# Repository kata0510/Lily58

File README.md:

# Lily58
Lily58 is 6*4+4keys column-staggered split keyboard.

## [Document Site Here](https://kata0510.github.io/Lily58-Document/)

# Type

- Lily58 Pro
  - [PCB Data](https://github.com/kata0510/Lily58/tree/master/Pro/PCB)
  - [BuildGuide JP](https://kata0510.github.io/Lily58-Document/Lily58_Pro_BG/)
  - [BuildGuide EN](https://github.com/kata0510/Lily58/blob/master/Pro/Doc/buildguide_en.md)
  - [BuildGuide IT](https://github.com/kata0510/Lily58/blob/master/Pro/Doc/buildguide_it.md)
  - [Shop(Yushakobo)](https://yushakobo.jp/shop/lily58-pro/)
- Lily58 Lite Rev2
  - [BuildGuide(YouTube)](https://www.youtube.com/watch?v=t6HLQvqlsVM)
  - [BuildInfo](https://kata0510.github.io/Lily58-Document/Lily58_Lite_Rev2_help.md)
  - [Shop(BOOTH)](https://booth.pm/ja/items/1963895)
  - [Shop(Yushakobo)](https://yushakobo.jp/shop/consign_lily58-lite-rev2/)
- Lily58(Old)
  - [PCB Data](https://github.com/kata0510/Lily58/tree/master/pcb)
  - [BuildGuide](https://kata0510.github.io/Lily58-Document/Lily58_BG/)
- Lily58 Lite Rev1(Old)
  - [PCB Data](https://github.com/kata0510/Lily58/tree/master/pcb)
  - [BuildGuide](https://kata0510.github.io/Lily58-Document/Lily58_Lite_BG/)

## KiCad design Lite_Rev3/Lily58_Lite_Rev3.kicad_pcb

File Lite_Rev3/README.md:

# Lily58 Lite Rev3

### description
- Controller: RP2040-Zero
- Firmware: QMK Firmware

### Assembly Guide
- https://docs.liliums.net/lily58-lite-rev3/about/ (RP2040 installed kit Version)

### Shop
- https://shop.liliums.net/products/lily58-lite-rev3
- https://shop.yushakobo.jp/products/9651

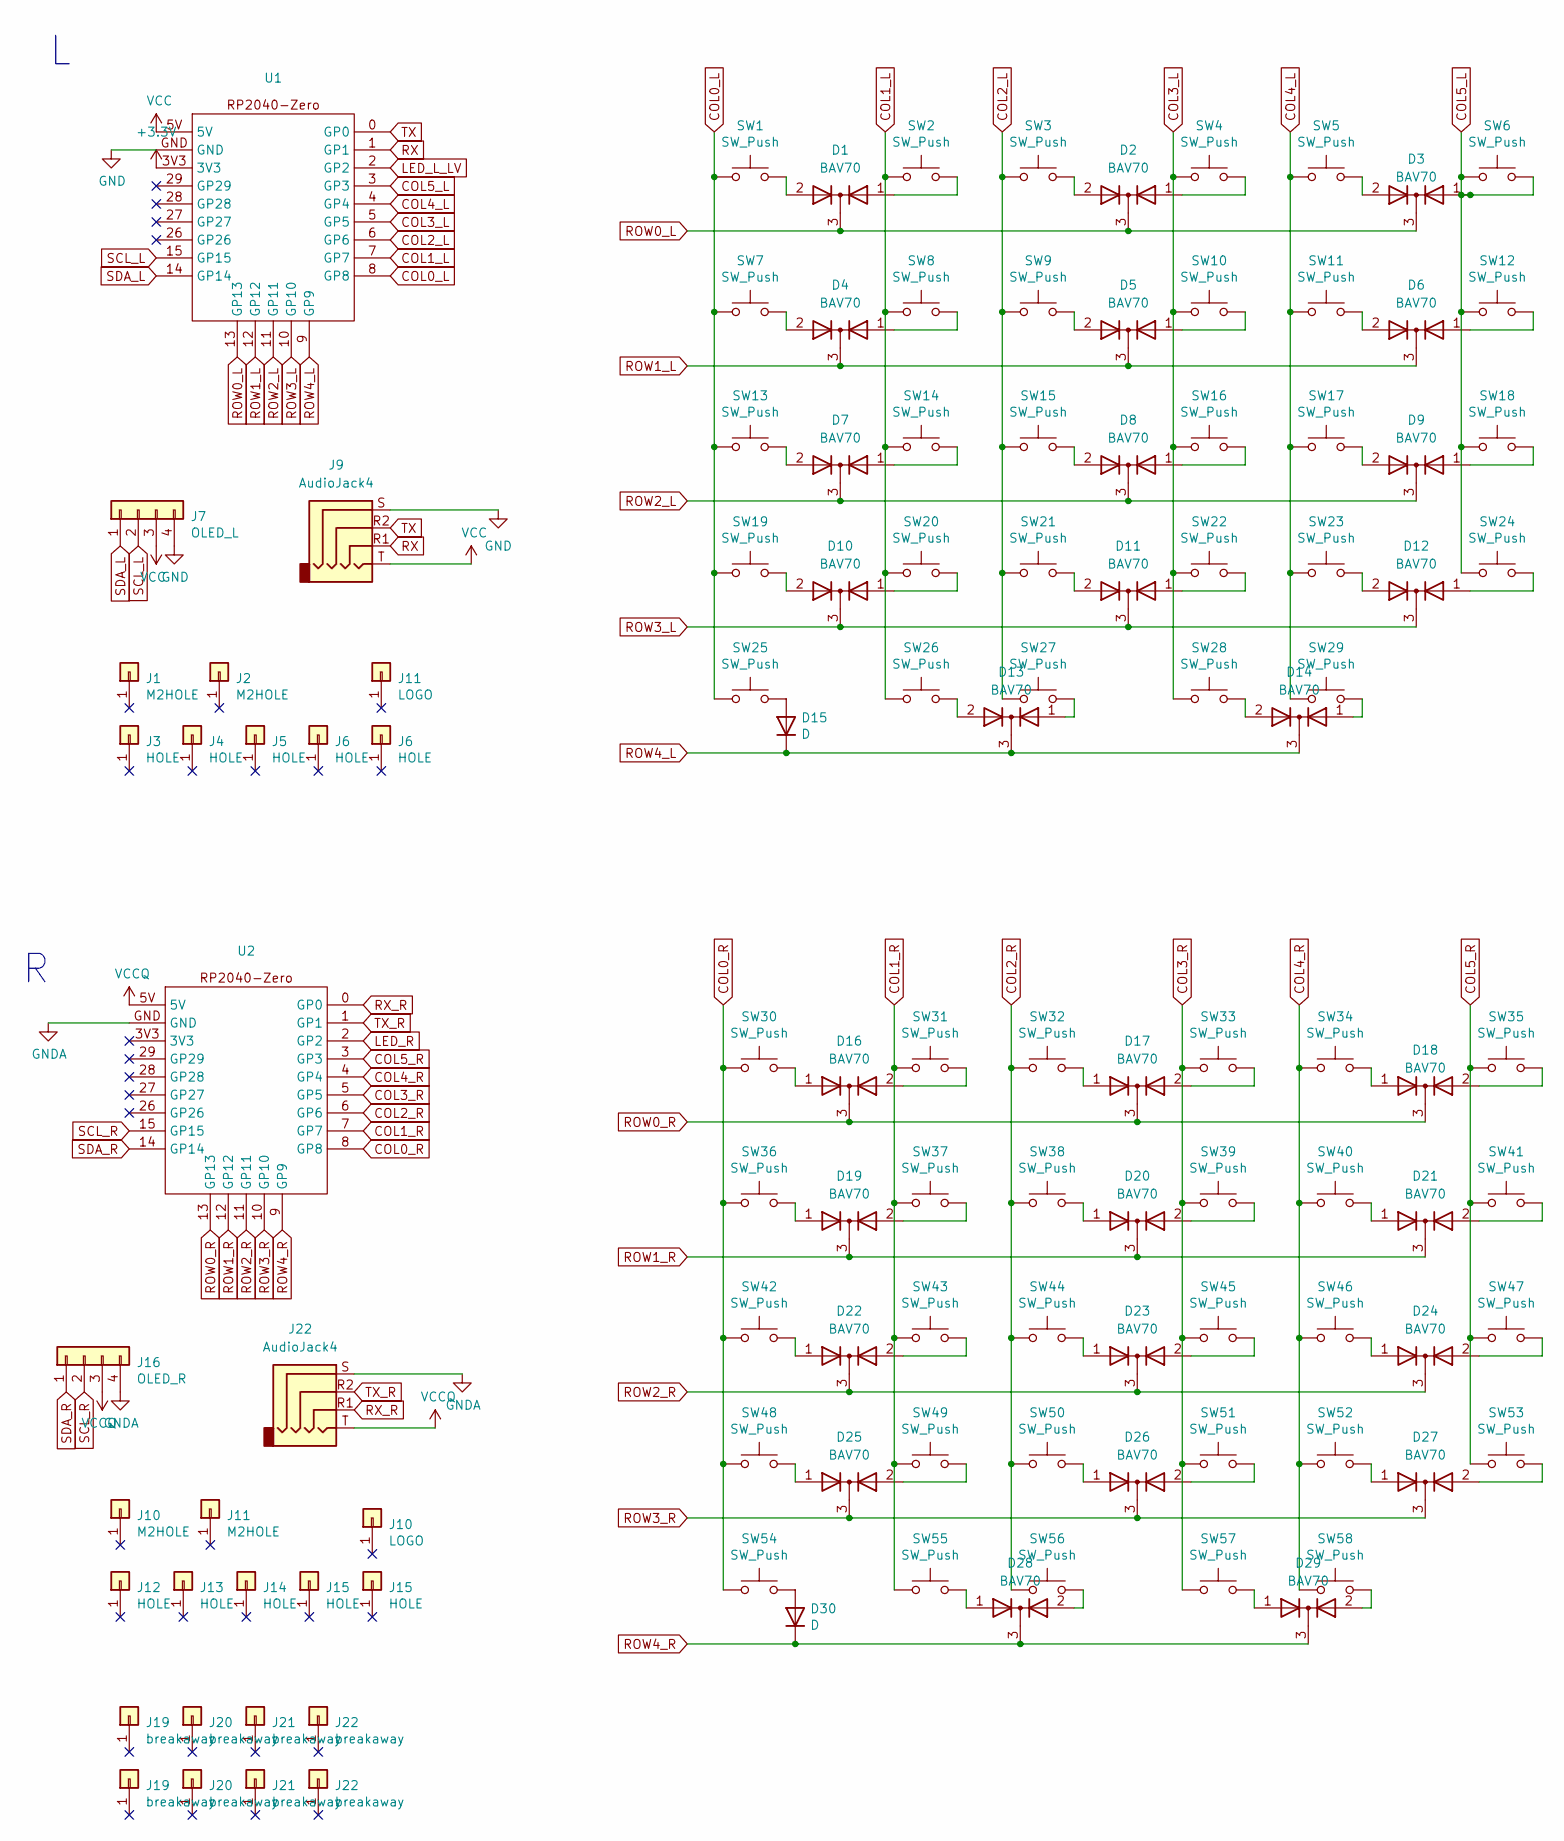
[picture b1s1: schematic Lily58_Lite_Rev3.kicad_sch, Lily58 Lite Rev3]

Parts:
D1, D2, D3, D4, D5, D6, D7, D8, D9, D10, D11, D12, D13, D14, D16, D17, D18, D19, D20, D21, D22, D23, D24, D25, D26, D27, D28, D29: BAV70; SOT-23
D15, D30: D; D_SOD-123
J1, J2, J11: M2HOLE; M2_HOLE_PCB
J3, J4, J5, J6, J12, J13, J14, J15: HOLE; HOLE_M2_TH
J7: OLED_L; OLED_4Pin
J9: AudioJack4; PJ-320
J10: LOGO; lily58_logo_2
J16: OLED_R; OLED_4Pin
J19, J20, J21, J22: breakaway; breakaway04
SW1, SW2, SW3, SW4, SW5, SW6, SW7, SW8, SW9, SW10, SW11, SW12, SW13, SW14, SW15, SW16, SW17, SW18, SW19, SW20, SW21, SW22, SW23, SW24, SW25, SW26, SW27, SW28, SW29, SW30, SW31, SW32, SW33, SW34, SW35, SW36, SW37, SW38, SW39, SW40, SW41, SW42, SW43, SW44, SW45, SW46, SW47, SW48, SW49, SW50, SW51, SW52, SW53, SW54, SW55, SW56, SW57, SW58: SW_Push; MX_HOLE
U1, U2: RP2040-Zero_bottom

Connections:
+3.3V: U1.3V3
COL0_L: SW1.1, SW7.1, SW13.1, SW19.1, SW25.1, U1.8 (GP8)
COL0_R: SW30.1, SW36.1, SW42.1, SW48.1, SW54.1, U2.8 (GP8)
COL1_L: SW2.1, SW8.1, SW14.1, SW20.1, SW26.1, U1.7 (GP7)
COL1_R: SW31.1, SW37.1, SW43.1, SW49.1, SW55.1, U2.7 (GP7)
COL2_L: SW3.1, SW9.1, SW15.1, SW21.1, SW27.1, U1.6 (GP6)
COL2_R: SW32.1, SW38.1, SW44.1, SW50.1, SW56.1, U2.6 (GP6)
COL3_L: SW4.1, SW10.1, SW16.1, SW22.1, SW28.1, U1.5 (GP5)
COL3_R: SW33.1, SW39.1, SW45.1, SW51.1, SW57.1, U2.5 (GP5)
COL4_L: SW5.1, SW11.1, SW17.1, SW23.1, SW29.1, U1.4 (GP4)
COL4_R: SW34.1, SW40.1, SW46.1, SW52.1, SW58.1, U2.4 (GP4)
COL5_R: SW35.1, SW41.1, SW47.1, SW53.1, U2.3 (GP3)
GND: J7.4, J9.S, U1.GND
GNDA: J16.4, J22.S, U2.GND
LED_L_LV: U1.2 (GP2)
LED_R: U2.2 (GP2)
unnamed: D1.1 (A), SW2.2
unnamed: D1.2 (A), SW1.2
unnamed: D2.1 (A), SW4.2
unnamed: D2.2 (A), SW3.2
unnamed: D3.2 (A), SW5.2
unnamed: D4.1 (A), SW8.2
unnamed: D4.2 (A), SW7.2
unnamed: D5.1 (A), SW10.2
unnamed: D5.2 (A), SW9.2
unnamed: D6.1 (A), SW12.2
unnamed: D6.2 (A), SW11.2
unnamed: D7.1 (A), SW14.2
unnamed: D7.2 (A), SW13.2
unnamed: D8.1 (A), SW16.2
unnamed: D8.2 (A), SW15.2
unnamed: D9.1 (A), SW18.2
unnamed: D9.2 (A), SW17.2
unnamed: D10.1 (A), SW20.2
unnamed: D10.2 (A), SW19.2
unnamed: D11.1 (A), SW22.2
unnamed: D11.2 (A), SW21.2
unnamed: D12.1 (A), SW24.2
unnamed: D12.2 (A), SW23.2
unnamed: D13.1 (A), SW27.2
unnamed: D13.2 (A), SW26.2
unnamed: D14.1 (A), SW29.2
unnamed: D14.2 (A), SW28.2
unnamed: D15.2 (A), SW25.2
unnamed: D16.1 (A), SW30.2
unnamed: D16.2 (A), SW31.2
unnamed: D17.1 (A), SW32.2
unnamed: D17.2 (A), SW33.2
unnamed: D18.1 (A), SW34.2
unnamed: D18.2 (A), SW35.2
unnamed: D19.1 (A), SW36.2
unnamed: D19.2 (A), SW37.2
unnamed: D20.1 (A), SW38.2
unnamed: D20.2 (A), SW39.2
unnamed: D21.1 (A), SW40.2
unnamed: D21.2 (A), SW41.2
unnamed: D22.1 (A), SW42.2
unnamed: D22.2 (A), SW43.2
unnamed: D23.1 (A), SW44.2
unnamed: D23.2 (A), SW45.2
unnamed: D24.1 (A), SW46.2
unnamed: D24.2 (A), SW47.2
unnamed: D25.1 (A), SW48.2
unnamed: D25.2 (A), SW49.2
unnamed: D26.1 (A), SW50.2
unnamed: D26.2 (A), SW51.2
unnamed: D27.1 (A), SW52.2
unnamed: D27.2 (A), SW53.2
unnamed: D28.1 (A), SW55.2
unnamed: D28.2 (A), SW56.2
unnamed: D29.1 (A), SW57.2
unnamed: D29.2 (A), SW58.2
unnamed: D30.2 (A), SW54.2
RESET_L: U1.26 (GP26)
RESET_R: U2.26 (GP26)
ROW0_L: D1.3 (K), D2.3 (K), D3.3 (K), U1.13 (GP13)
ROW0_R: D16.3 (K), D17.3 (K), D18.3 (K), U2.13 (GP13)
ROW1_L: D4.3 (K), D5.3 (K), D6.3 (K), U1.12 (GP12)
ROW1_R: D19.3 (K), D20.3 (K), D21.3 (K), U2.12 (GP12)
ROW2_L: D7.3 (K), D8.3 (K), D9.3 (K), U1.11 (GP11)
ROW2_R: D22.3 (K), D23.3 (K), D24.3 (K), U2.11 (GP11)
ROW3_L: D10.3 (K), D11.3 (K), D12.3 (K), U1.10 (GP10)
ROW3_R: D25.3 (K), D26.3 (K), D27.3 (K), U2.10 (GP10)
ROW4_L: D13.3 (K), D14.3 (K), D15.1 (K), U1.9 (GP9)
ROW4_R: D28.3 (K), D29.3 (K), D30.1 (K), U2.9 (GP9)
RX: J9.R1, U1.1 (GP1)
RX_R: J22.R1, U2.0 (GP0)
SCL_L: J7.2, U1.15 (GP15)
SCL_R: J16.2, U2.15 (GP15)
SDA_L: J7.1, U1.14 (GP14)
SDA_R: J16.1, U2.14 (GP14)
TX: J9.R2, U1.0 (GP0)
TX_R: J22.R2, U2.1 (GP1)
VCC: J7.3, J9.T, U1.5V
VCCQ: J16.3, J22.T, U2.5V

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
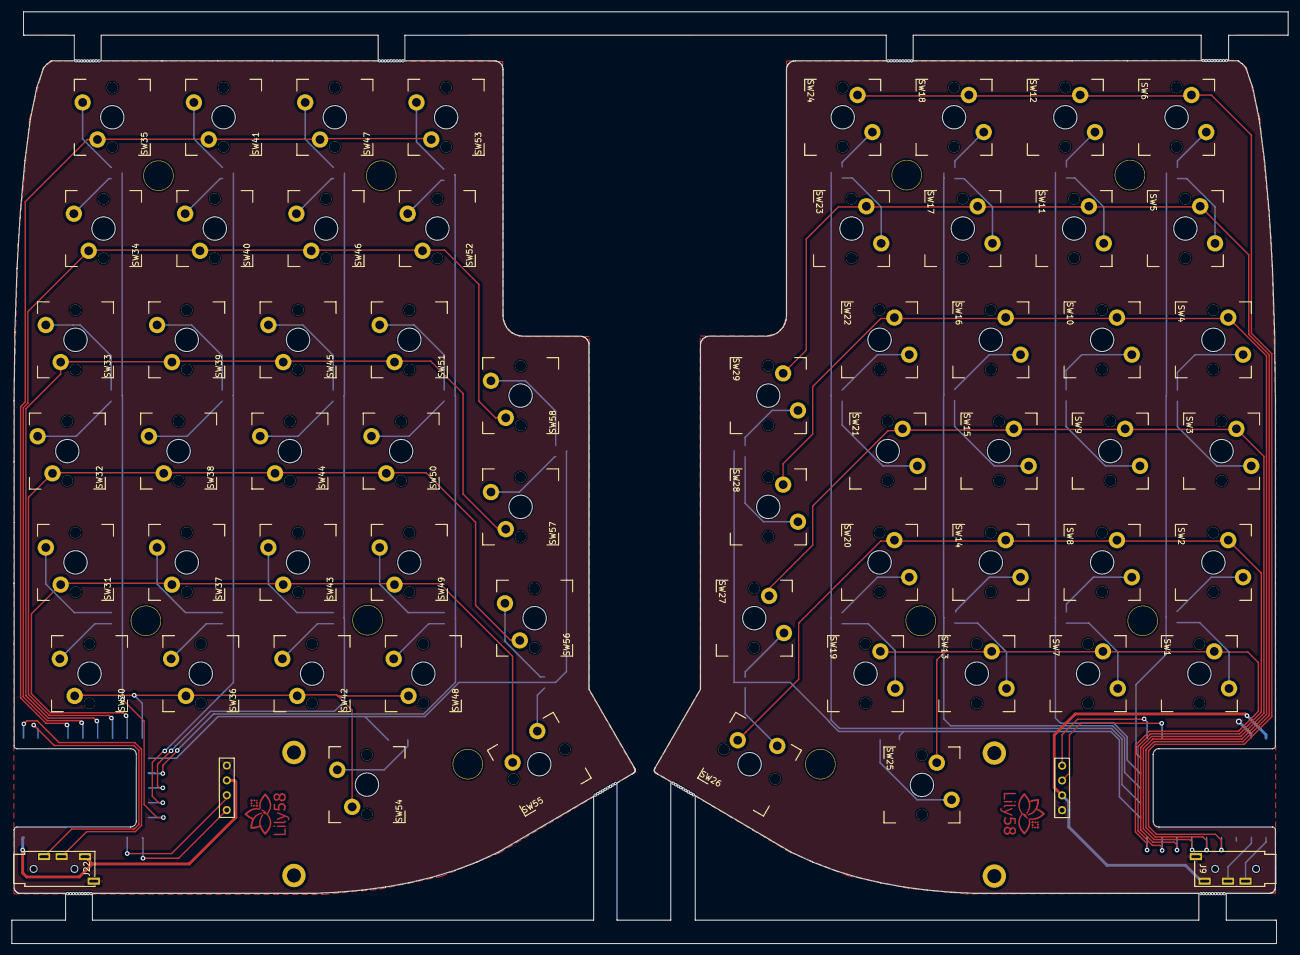
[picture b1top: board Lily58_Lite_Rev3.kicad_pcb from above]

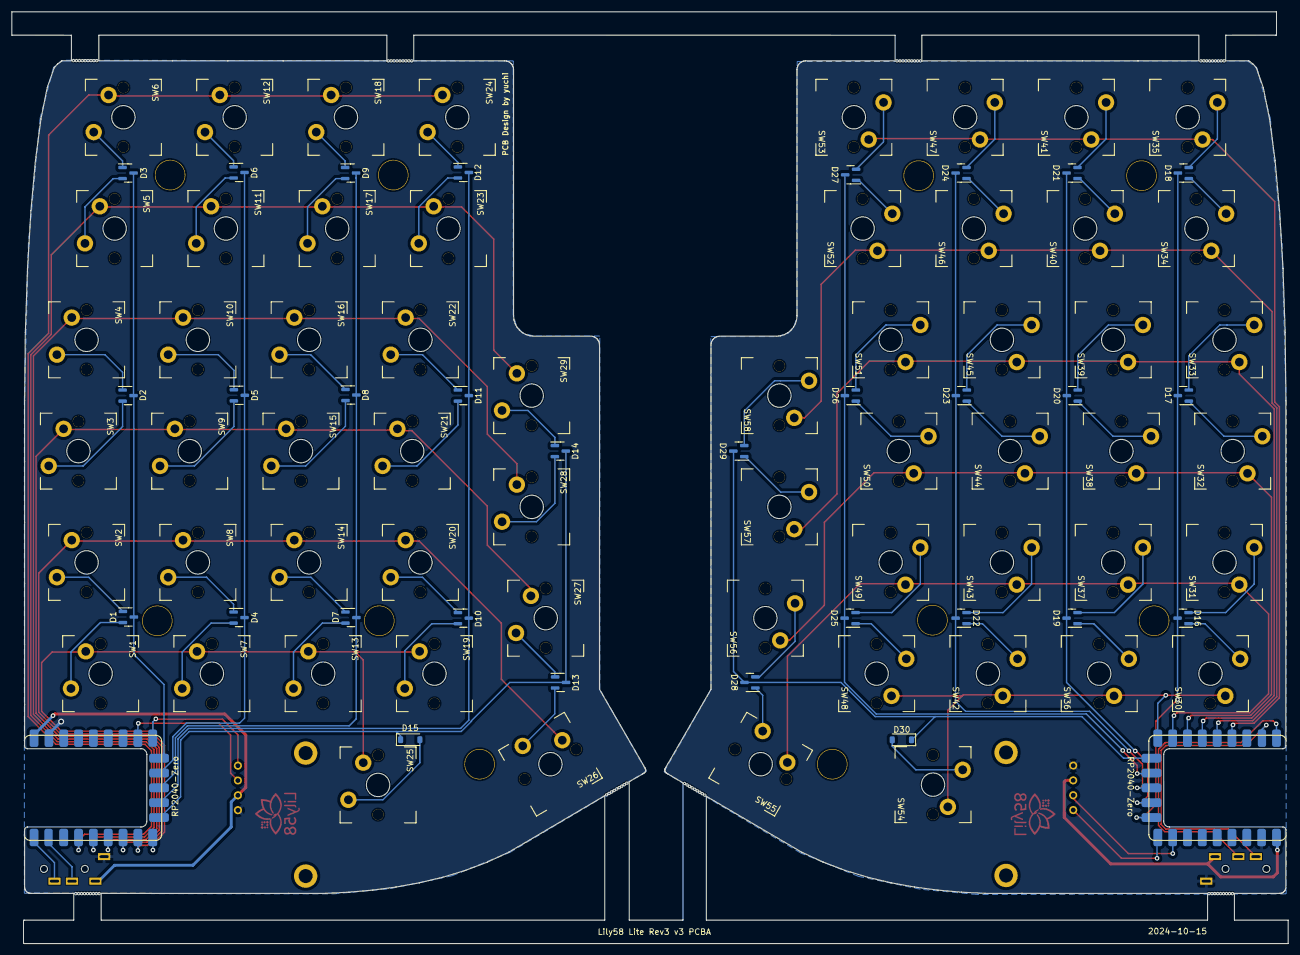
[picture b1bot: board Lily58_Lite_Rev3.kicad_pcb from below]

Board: 2 copper layers, 218.5 x 159.5 mm, 118 parts (34 on the bottom side), 92 nets.

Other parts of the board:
J8, J17, J18, J25, J26: breakaway; breakaway04
J23, J24: HOLE; HOLE_M2_TH_5mm
L01, L02: LOGO; lily58_logo_2

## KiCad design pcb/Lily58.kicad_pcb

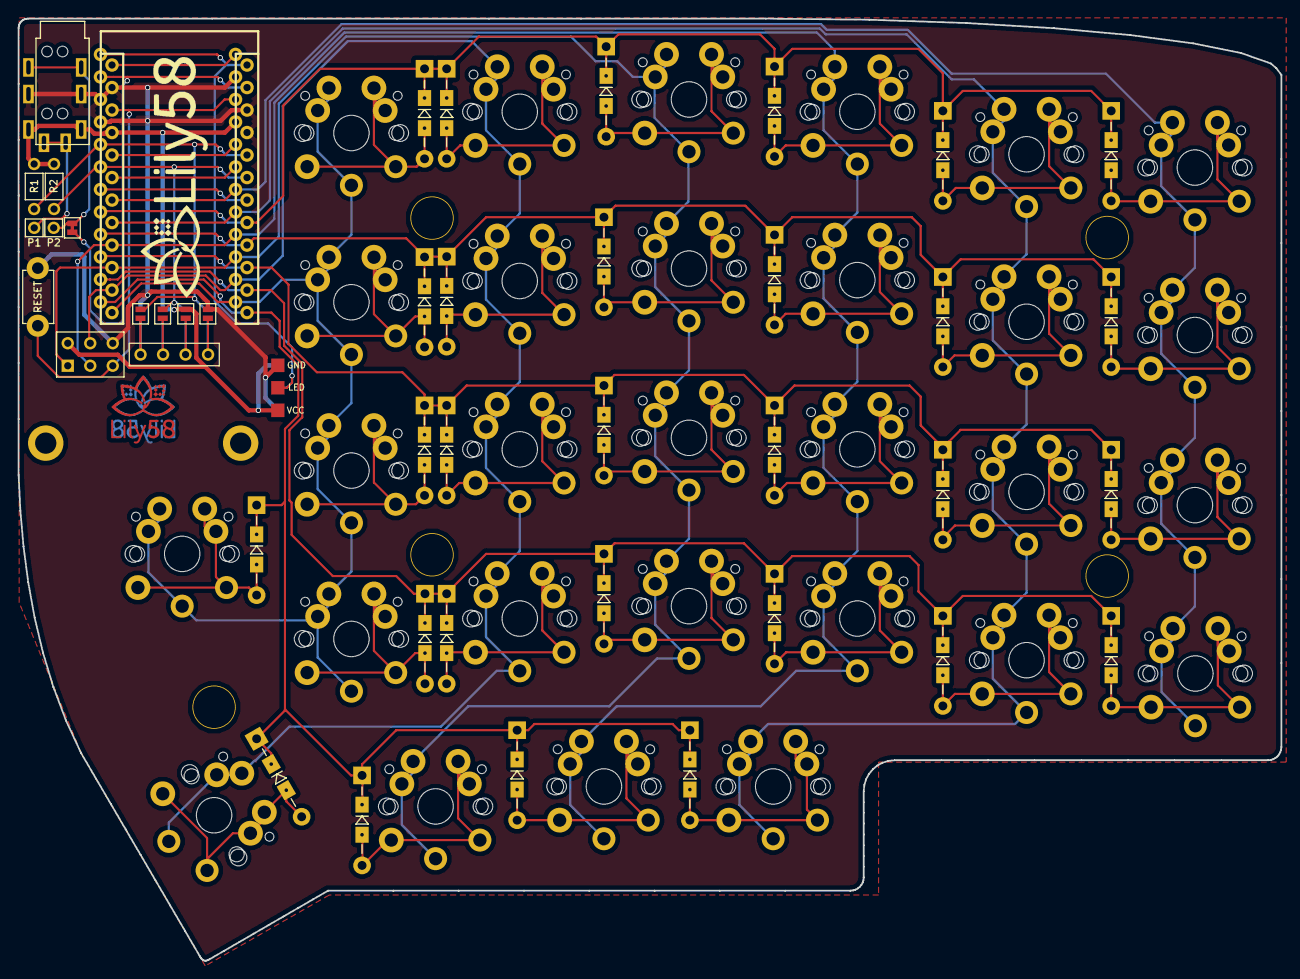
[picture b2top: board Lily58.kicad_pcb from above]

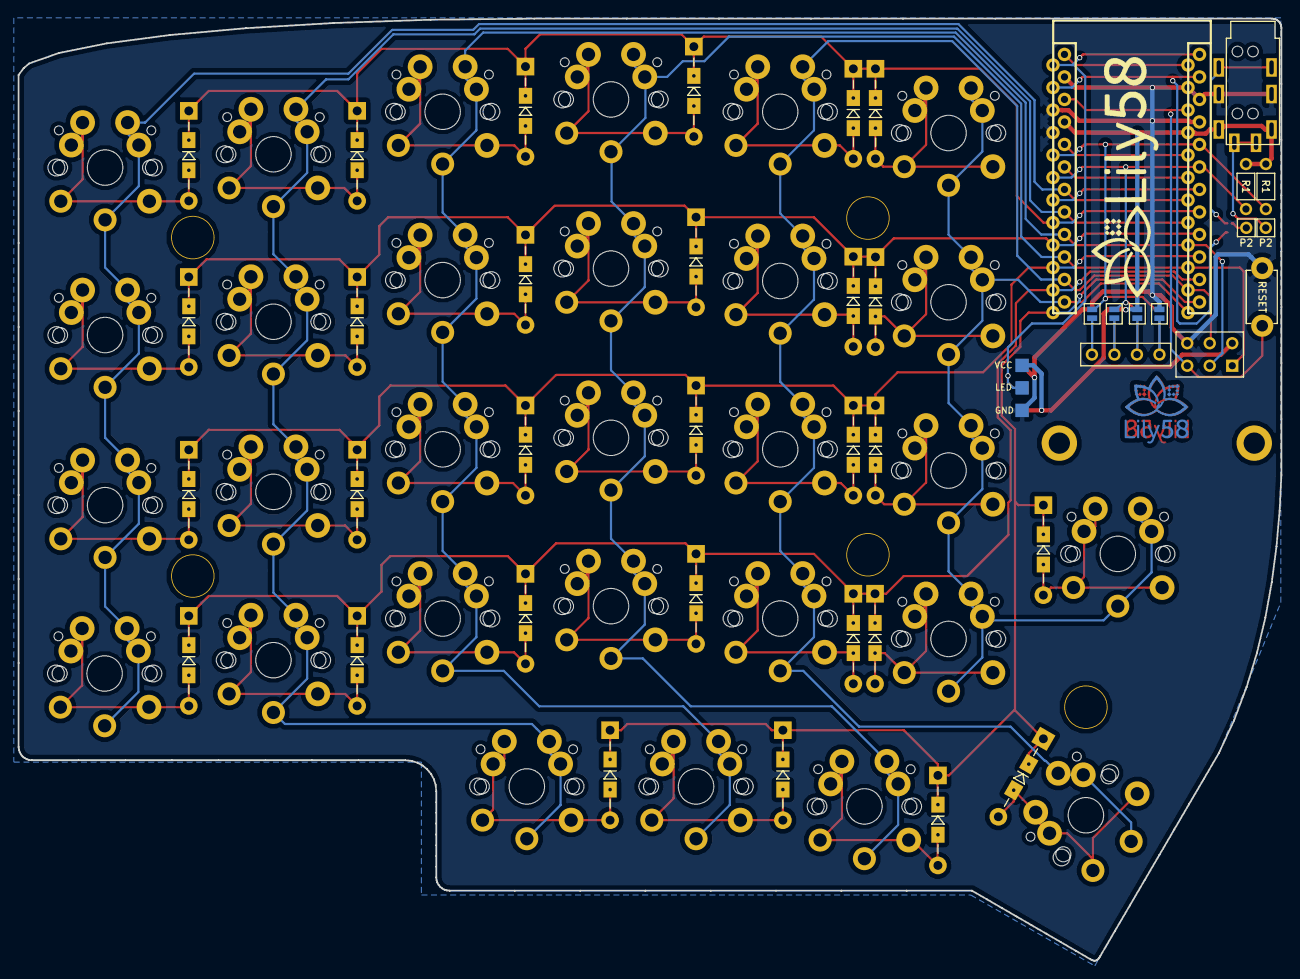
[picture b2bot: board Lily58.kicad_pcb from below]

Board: 2 copper layers, 142.5 x 106.3 mm, 84 parts (4 on the bottom side), 53 nets.

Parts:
D1, D2, D3, D4, D5, D6, D7, D8, D9, D10, D11, D12, D13, D14, D15, D16, D17, D18, D19, D20, D21, D22, D23, D24, D25, D26, D27, D28, D29: D; Diode_TH_SOD123
J1: LED; StripLED
J2: 4PIN; MJ-4PP-9
JP1, JP2, JP3, JP4, JP5, JP6, JP7, JP8: Jumper
OLED: OLED; MY_SIL-4
P1, P2: i2c_pin; 1pin_conn
P3: ICSP
R1, R2: R; RESISTOR_mini
RSW1: SW_RST; TACT_SWITCH_TVBP06
SW1, SW2, SW3, SW4, SW5, SW6, SW7, SW8, SW9, SW10, SW11, SW12, SW13, SW14, SW15, SW16, SW17, SW18, SW19, SW20, SW21, SW22, SW23, SW24, SW25, SW27, SW28, SW29: SW_PUSH; MX_PG1350-Under_FLIP_HOLES_18mm
SW26: SW_PUSH; MX_PG1350-Under_FLIP_HOLES_27mm
TH1, TH2: HOLE; M2_HOLE_PCB
TH3, TH4, TH5, TH6, TH7: HOLE; HOLE_M2_TH
U1: ProMicro; ProMicro_rev2
W1: jumper; jumper_data

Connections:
DATA: U1.2, W1.1
GND: J1.3, J2.2, JP1.2, JP8.2, P3.6, RSW1.1, U1.3, U1.4, U1.23
LED: J1.2, U1.1
unnamed: D1.2, SW1.2
unnamed: D2.2, SW2.2
unnamed: D3.2, SW3.2
unnamed: D4.2, SW4.2
unnamed: D5.2, SW5.2
unnamed: D6.2, SW6.2
unnamed: D7.2, SW7.2
unnamed: D8.2, SW8.2
unnamed: D9.2, SW9.2
unnamed: D10.2, SW10.2
unnamed: D11.2, SW11.2
unnamed: D12.2, SW12.2
unnamed: D13.2, SW13.2
unnamed: D14.2, SW14.2
unnamed: D15.2, SW15.2
unnamed: D16.2, SW16.2
unnamed: D17.2, SW17.2
unnamed: D18.2, SW18.2
unnamed: D19.2, SW19.2
unnamed: D20.2, SW20.2
unnamed: D21.2, SW21.2
unnamed: D22.2, SW22.2
unnamed: D23.2, SW23.2
unnamed: D24.2, SW24.2
unnamed: D25.2, SW25.2
unnamed: D26.2, SW26.2
unnamed: D27.2, SW27.2
unnamed: D28.2, SW28.2
unnamed: D29.2, SW29.2
unnamed: J2.3, P2.1, W1.2
unnamed: J2.4, P1.1
unnamed: JP1.1, JP5.1, OLED.4
unnamed: JP2.1, JP6.1, OLED.3
unnamed: JP3.1, JP7.1, OLED.2
unnamed: JP4.1, JP8.1, OLED.1
RESET: P3.5, RSW1.2, U1.22
SCL: JP3.2, JP6.2, R2.2, U1.6
SDA: JP4.2, JP5.2, R1.2, U1.5
VCC: J1.1, J2.1, JP2.2, JP7.2, P3.2, R1.1, R2.1, U1.21
col0: SW6.1, SW12.1, SW18.1, SW24.1, U1.18
col1: SW5.1, SW11.1, SW17.1, SW23.1, SW29.1, U1.17
col2: P3.3, SW4.1, SW10.1, SW16.1, SW22.1, SW28.1, U1.16
col3: P3.1, SW3.1, SW9.1, SW15.1, SW21.1, SW27.1, U1.15
col4: P3.4, SW2.1, SW8.1, SW14.1, SW20.1, SW26.1, U1.14
col5: SW1.1, SW7.1, SW13.1, SW19.1, SW25.1, U1.13
row0: D1.1, D2.1, D3.1, D4.1, D5.1, D6.1, U1.8
row1: D7.1, D8.1, D9.1, D10.1, D11.1, D12.1, U1.9
row2: D13.1, D14.1, D15.1, D16.1, D17.1, D18.1, U1.10
row3: D19.1, D20.1, D21.1, D22.1, D23.1, D24.1, U1.11
row4: D25.1, D26.1, D27.1, D28.1, D29.1, U1.12

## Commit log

2018-08-21 add PCB
2018-08-21 add case data
2018-08-29 fix case
2018-09-06 update other
2018-09-07 Add LICENSE
2018-09-11 fix and update README
2018-10-13 add buildguide
2018-10-21 file fix
2018-10-22 fix PCB
2018-10-22 buildguide add keymap
2018-10-25 README typo fix
2018-11-09 add doc
2018-11-21 Update Document
2018-12-26 add pro doc
2018-12-31 Lily58Pro Buildguide Update
2019-01-06 Update ProBuildguide
2019-01-13 Update BuildGuide
2019-01-30 Pro BuildGuide Update
2019-01-30 fix buildguide
2019-02-05 Add Lily58 Pro PCB Data
2019-02-23 Add Lily58 Pro PCBData
2019-02-23 Lily58 PCBData update
2019-02-28 update pro buildguide
2019-03-01 Pro Buildguide fix
2019-03-01 README Photo Update
2019-06-05 Add English translation of the build guide for the Pro kit. I don't speak Japanese, so this is a rough translation based on Google Translate and some experience building this board.
2019-07-02 Update Lily58_Lite Buildguide
2019-07-20 Update buildguide_en.md
    remove wrong space in make rule.
2019-07-20 Update buildguide_en.md
    actually also space after colon should be removed.
2019-07-25 fix lily58 lite buildguide
2019-08-20 Update Lily58 Lite buildguide
2020-04-30 add lite_rev2 info
2020-05-02 update lite_rev2 info
2020-05-16 Add first rev of the Lily58L build guide
2020-05-16 Add firmware link to readme
2020-06-03 Added section for rotary encoder
2020-07-21 Correctly formats nested list
2020-07-28 Update Lite LiteRev2 Buildguide
2020-08-10 Add DocmentPage
2020-08-13 Fix README.md
2020-09-18 Add info's for rotary, oled and led installation and more (#2)
    * added some modification to the build guide
    * some changes on the builguide
    * Update buildguide_en.md
    * Update buildguide_en.md
2020-09-18 Small typo
2020-09-18 Add placeholder for missing images
2020-09-18 Add build-guide link and info for building firmware
2020-09-23 fix Lily58 PCB
2020-09-23 fix Lily58 Pro PCB outline #13
2020-12-21 update the build commands and add toc
2020-12-21 update new build command
2021-02-04 add how to bridge underglow leds
2021-05-15 add puchi-c to part list
2021-05-15 markdown formatting
2021-05-15 add schematic
2021-05-15 add badges
2021-09-04 Add spell check with reviewdog (misspell)
2021-09-04 Added advice for Pro Micro orientation.
2021-09-04 Fix spelling in file names
2022-08-07 fix Lily58 Pro BuildGuide
2022-09-25 change url to new document
2022-11-12 update url
    update url form document site
2022-12-04 Add Lily58 Pro Rev2(RP2040)
2022-12-06 Add English translation for Lili58 build guide
2022-12-06 Fix grammar and spelling errors
2022-12-18 fix DocmentLink
2022-12-18 Pro/Doc/buildguide_en.md: link to english helix buildguide, not japanese
    also: not so WIP anymore
2023-01-05 Create buildguide_it.md
    Introduce first version of Italian translation.
2023-01-16 Update README.md
    Add Italian guide
2023-01-26 Add instructions for promicro facing
2023-08-15 add Lily58 Pro Rev2 PCB
2024-02-03 Update Lily58 ProRev2
2024-07-15 Update Lily58 Pro V2
2024-07-15 rename to Lily58 Pro V2
2024-07-24 Pro v2 update
2024-07-24 Lily58 Pro v2 Rename
2024-07-24 add Lily58 Lite Rev3
2024-07-24 refactor folder structure
2024-07-25 add Lily58 Pro v2 README
2024-07-28 [Lily58 Pro v2]: Update README
2024-07-30 [Lily58 Lite Rev3] Fix silk rotate
2024-09-02 [Lily58 Lite Rev3] fix cols pin
    Changed to the same cols pin as Lily58 Pro and Lily58 Pro v2
2024-10-24 [Lily58 Lite Rev3] Fix SW54
2024-10-24 add gitignore
2024-10-24 [Lily58 Lite Rev3] Add README
2024-10-24 [Lily58 Pro v2]Update README
2024-12-22 [Lily58 Lite Rev3] fix PCB
2024-12-22 add PCB Top Plate
2025-10-07 Create buildguide_es.md
    Added the Spanish version of the build guide.
2025-10-07 update some Spanish typos
2025-12-26 fix SPLIT_HAND_PIN_L Pin #57
